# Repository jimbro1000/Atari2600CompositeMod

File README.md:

# Atari 2600 Composite Video Mod #

This repository contains a hardware design
of a composite video mod to fit the Atari
2600 VCS

## Design ##

The project is built in KiCad 7

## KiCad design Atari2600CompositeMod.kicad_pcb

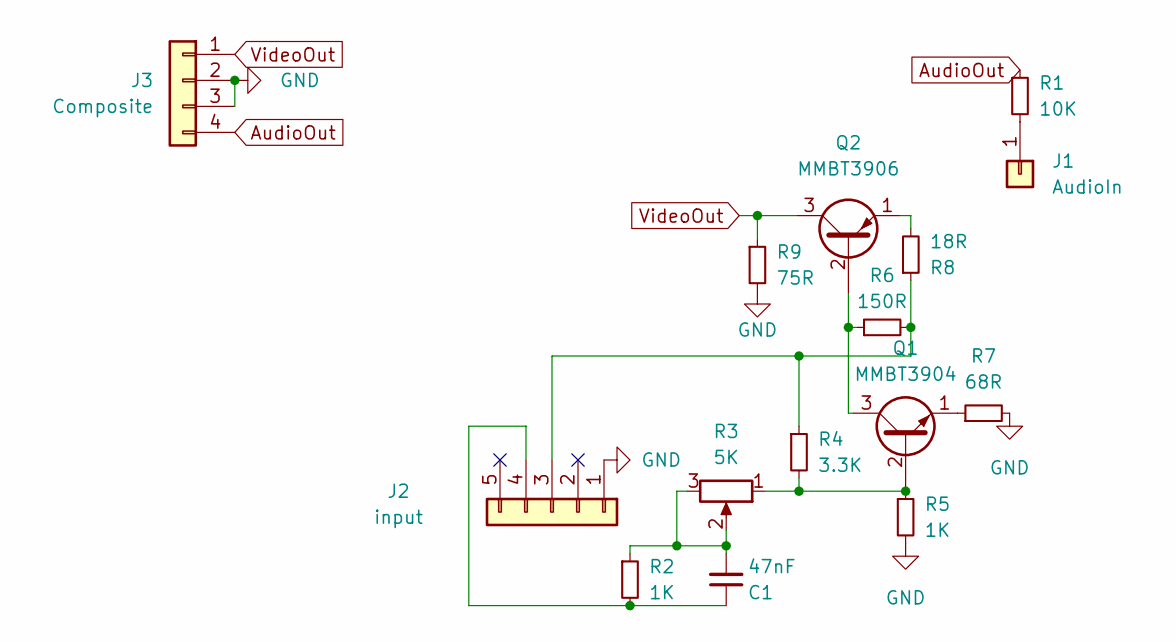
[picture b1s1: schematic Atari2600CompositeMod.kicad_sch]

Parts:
C1: 47nF; C_0805_2012Metric_Pad1.18x1.45mm_HandSolder
J1: AudioIn; TestPoint_THTPad_1.0x1.0mm_Drill0.5mm
J2: input; PinHeader_1x05_P2.54mm_Horizontal
J3: Composite; PinHeader_1x04_P2.54mm_Horizontal
Q1: MMBT3904; SOT-23-3
Q2: MMBT3906; SOT-23-3
R1: 10K; R_0805_2012Metric_Pad1.20x1.40mm_HandSolder
R2, R5: 1K; R_0805_2012Metric_Pad1.20x1.40mm_HandSolder
R3: 5K; Potentiometer_Bourns_3386C_Horizontal
R4: 3.3K; R_0805_2012Metric_Pad1.20x1.40mm_HandSolder
R6: 150R; R_0805_2012Metric_Pad1.20x1.40mm_HandSolder
R7: 68R; R_0805_2012Metric_Pad1.20x1.40mm_HandSolder
R8: 18R; R_0805_2012Metric_Pad1.20x1.40mm_HandSolder
R9: 75R; R_0805_2012Metric_Pad1.20x1.40mm_HandSolder

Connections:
AudioOut: J3.4, R1.1
GND: J2.1, J3.2, J3.3, R5.2, R7.2, R9.2
unnamed: C1.2, R2.1, R3.2, R3.3
unnamed: J1.1, R1.2
unnamed: J2.3, R4.1, R6.2, R8.1
unnamed: C1.1, J2.4, R2.2
unnamed: Q1.2 (B), R3.1, R4.2, R5.1
unnamed: Q1.3 (C), Q2.2 (B), R6.1
unnamed: Q1.1 (E), R7.1
unnamed: Q2.1 (E), R8.2
VideoOut: J3.1, Q2.3 (C), R9.1

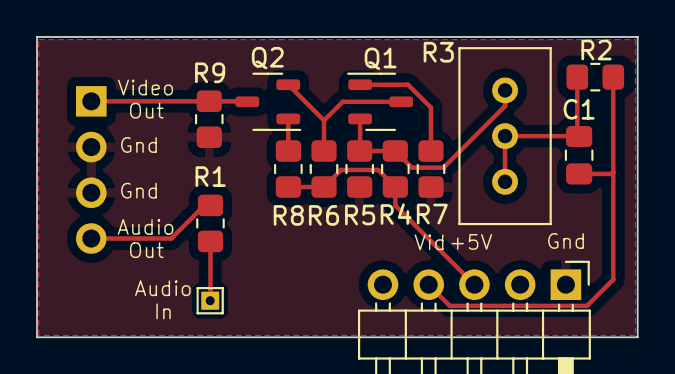
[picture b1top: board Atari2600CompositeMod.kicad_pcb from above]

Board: 2 copper layers, 33.4 x 16.7 mm, 15 parts (1 on the bottom side), 11 nets.

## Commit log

2024-02-10 convert board to smd
2024-02-10 add ibom
